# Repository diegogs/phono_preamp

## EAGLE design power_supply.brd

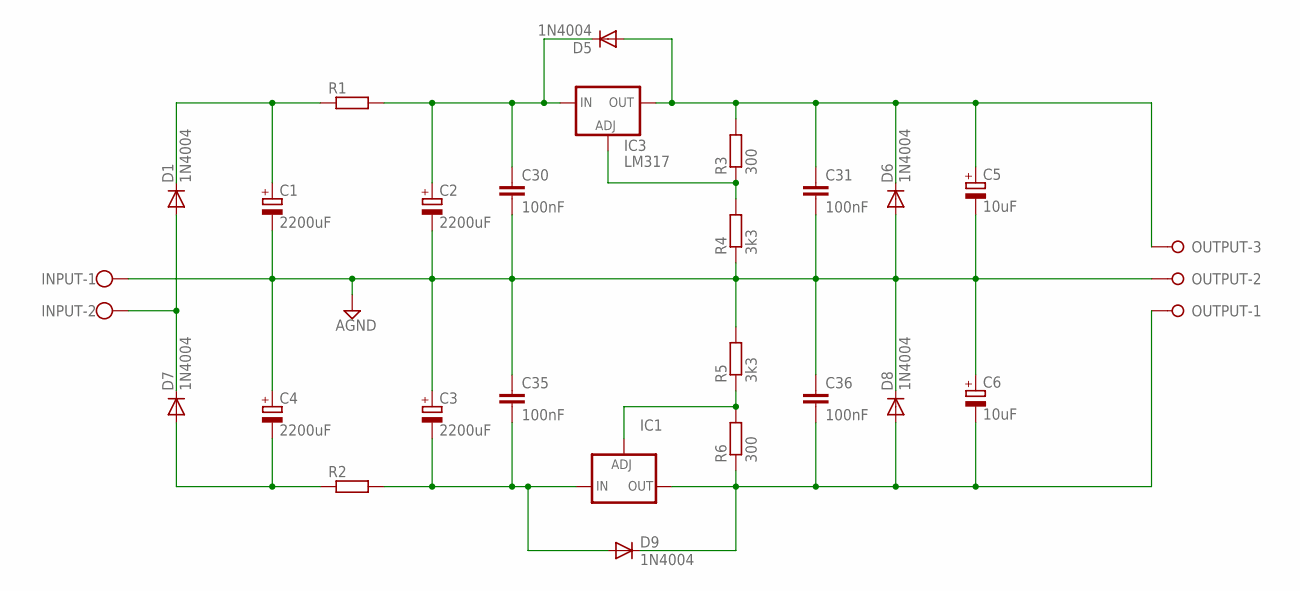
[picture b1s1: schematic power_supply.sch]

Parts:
C1, C2, C3, C4: 2200uF; E7,5-16
C5, C6: 10uF; E2,5-5
C30, C31, C35, C36: 100nF; C050-025X075
D1, D5, D6, D7, D8, D9: 1N4004; DO41-10
IC1: LM337TS; 337TS
IC3: LM317; 317TS
INPUT: W237-102
OUTPUT: W237-3E
R1, R2: R-EU_0207/10; 0207/10
R3, R6: 300; 0207/7
R4, R5: 3k3; 0207/7

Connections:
AGND: C1.-, C2.-, C3.+, C4.+, C5.-, C6.+, C30.2, C31.2, C35.1, C36.1, D6.A, D8.C, INPUT.1, OUTPUT.2, R4.1, R5.2
unnamed: IC1.1 (ADJ), R5.1, R6.2
unnamed: D1.A, D7.C, INPUT.2
unnamed: C6.-, C36.2, D8.A, D9.C, IC1.3 (OUT), OUTPUT.1, R6.1
unnamed: C5.+, C31.1, D5.A, D6.C, IC3.2 (OUT), OUTPUT.3, R3.2
unnamed: C2.+, C30.1, D5.C, IC3.3 (IN), R1.2
unnamed: IC3.1 (ADJ), R3.1, R4.2
unnamed: C1.+, D1.C, R1.1
unnamed: C3.-, C35.2, D9.A, IC1.2 (IN), R2.2
unnamed: C4.-, D7.A, R2.1

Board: 2 copper layers, 26 parts (26 on the bottom side), 10 nets, no tracks yet.

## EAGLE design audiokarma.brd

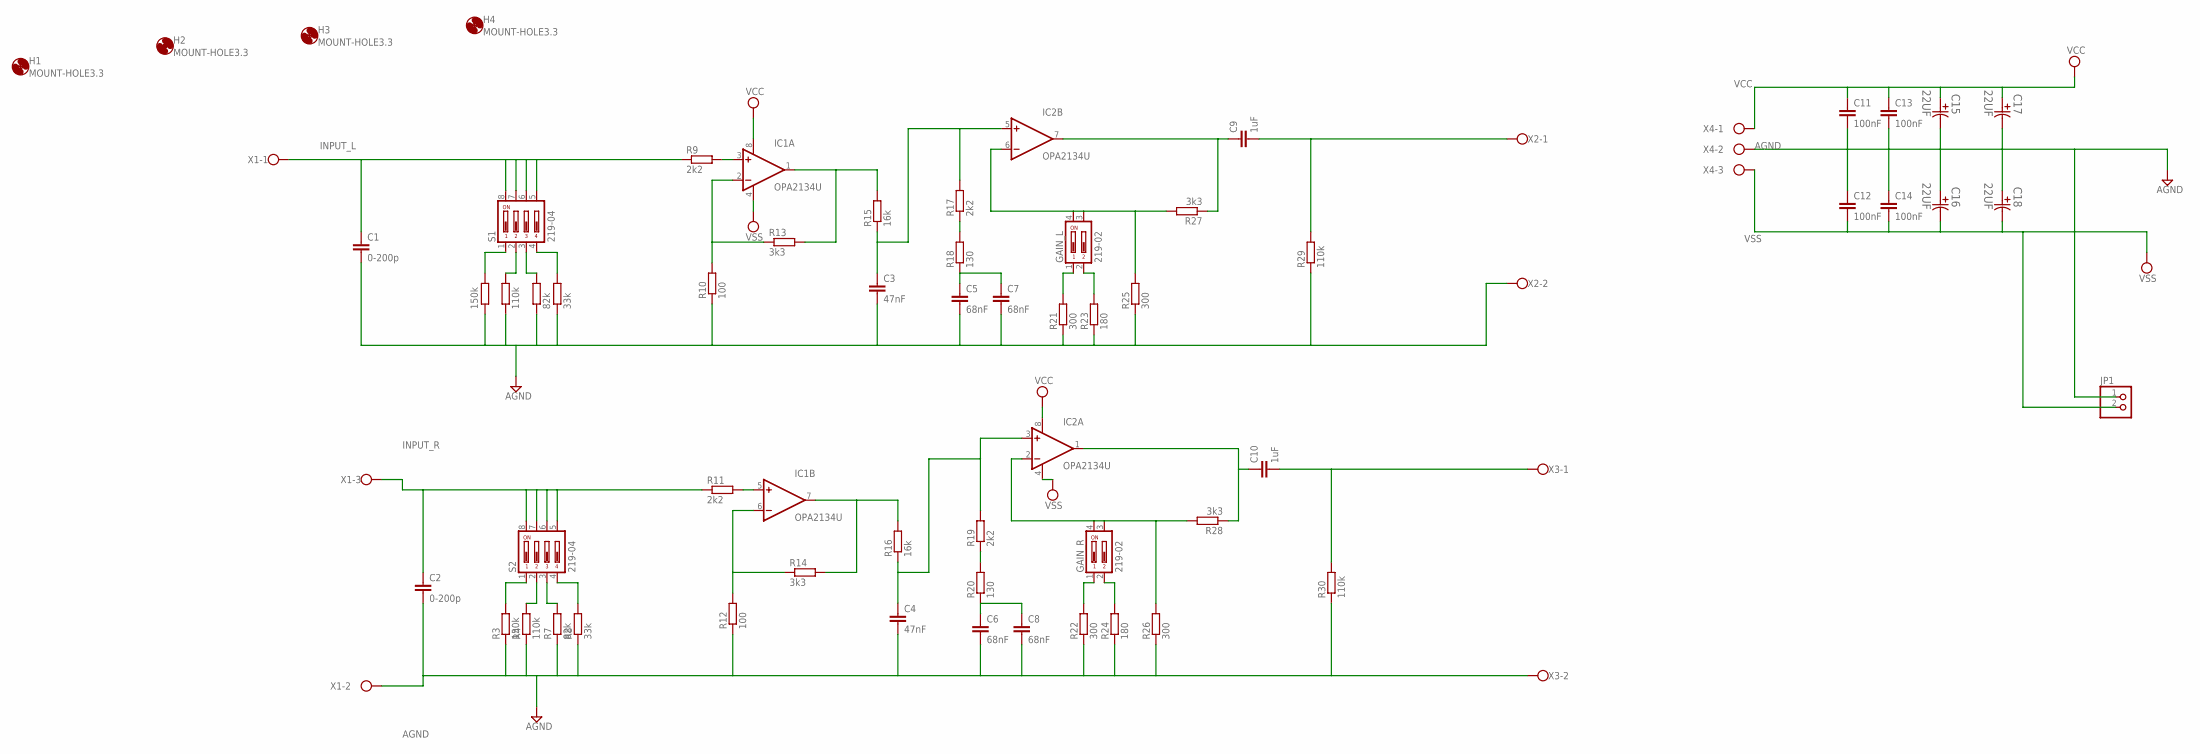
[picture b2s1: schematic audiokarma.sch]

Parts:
C1, C2: 0-200p; C0805
C3, C4: 47nF; C050-025X075
C5, C6, C7, C8: 68nF; C050-035X075
C9, C10: 1uF; C050-050X075
C11, C12, C13, C14: 100nF; C0805
C15, C16, C17, C18: 22UF; CAPAE830X650N
GAIN_L: 219-02; CTS-219-02
GAIN_R: 219-02; CTS-219-02
H1, H2, H3, H4: MOUNT-HOLE3.3; 3,3
IC1, IC2: OPA2134U; SO08
JP1: PINHD-1X2; 1X02
R1, R3: 150k; R0805
R2, R4, R29, R30: 110k; R0805
R5, R7: 82k; R0805
R6, R8: 33k; R0805
R9, R11, R17, R19: 2k2; R0805
R10, R12: 100; R0805
R13, R14, R27, R28: 3k3; R0805
R15, R16: 16k; R0805
R18, R20: 130; R0805
R21, R22, R25, R26: 300; R0805
R23, R24: 180; R0805
S1, S2: 219-04; CTS-219-04
X1, X4: W237-103
X2, X3: W237-102

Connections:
AGND: C1.2, C2.2, C3.2, C4.2, C5.2, C6.2, C7.2, C8.2, C11.2, C12.1, C13.2, C14.1, C15.2, C16.1, C17.2, C18.1, JP1.1, R1.1, R2.1, R3.1, R4.1, R5.1, R6.1, R7.1, R8.1, R10.1, R12.1, R21.1, R22.1, R23.1, R24.1, R25.1, R26.1, R29.1, R30.1, X1.2, X2.2, X3.2, X4.2
INPUT_L: C1.1, R9.1, S1.5, S1.6, S1.7, S1.8, X1.1
INPUT_R: C2.1, R11.1, S2.5, S2.6, S2.7, S2.8, X1.3
unnamed: R1.2, S1.1
unnamed: R2.2, S1.2
unnamed: R5.2, S1.3
unnamed: R6.2, S1.4
unnamed: C9.1, IC2.7 (OUT), R27.1
unnamed: R3.2, S2.1
unnamed: IC1.3 (+IN), R9.2
unnamed: IC1.2 (-IN), R10.2, R13.1
unnamed: C9.2, R29.2, X2.1
unnamed: IC1.1 (OUT), R13.2, R15.2
unnamed: C3.1, IC2.5 (+IN), R15.1, R17.2
unnamed: R4.2, S2.2
unnamed: R7.2, S2.3
unnamed: R8.2, S2.4
unnamed: C5.1, C7.1, R18.1
unnamed: R17.1, R18.2
unnamed: IC1.5 (+IN), R11.2
unnamed 20: GAIN_L.3, GAIN_L.4, IC2.6 (-IN), R25.2, R27.2; also elsewhere on the board
unnamed 21: GAIN_L.1, R21.2; also elsewhere on the board
unnamed 22: GAIN_L.2, R23.2; also elsewhere on the board
unnamed: IC1.6 (-IN), R12.2, R14.1
unnamed: IC1.7 (OUT), R14.2, R16.2
unnamed: C4.1, IC2.3 (+IN), R16.1, R19.2
unnamed: C6.1, C8.1, R20.1
unnamed: R19.1, R20.2
unnamed 28: GAIN_R.3, GAIN_R.4, IC2.2 (-IN), R26.2, R28.2; also elsewhere on the board
unnamed 29: GAIN_R.1, R22.2; also elsewhere on the board
unnamed 30: GAIN_R.2, R24.2; also elsewhere on the board
unnamed: C10.1, IC2.1 (OUT), R28.1
unnamed: C10.2, R30.2, X3.1
VCC: C11.1, C13.1, C15.1, C17.1, IC1.8 (V+), IC2.8 (V+), X4.1
VSS: C12.2, C14.2, C16.2, C18.2, IC1.4 (V-), IC2.4 (V-), JP1.2, X4.3

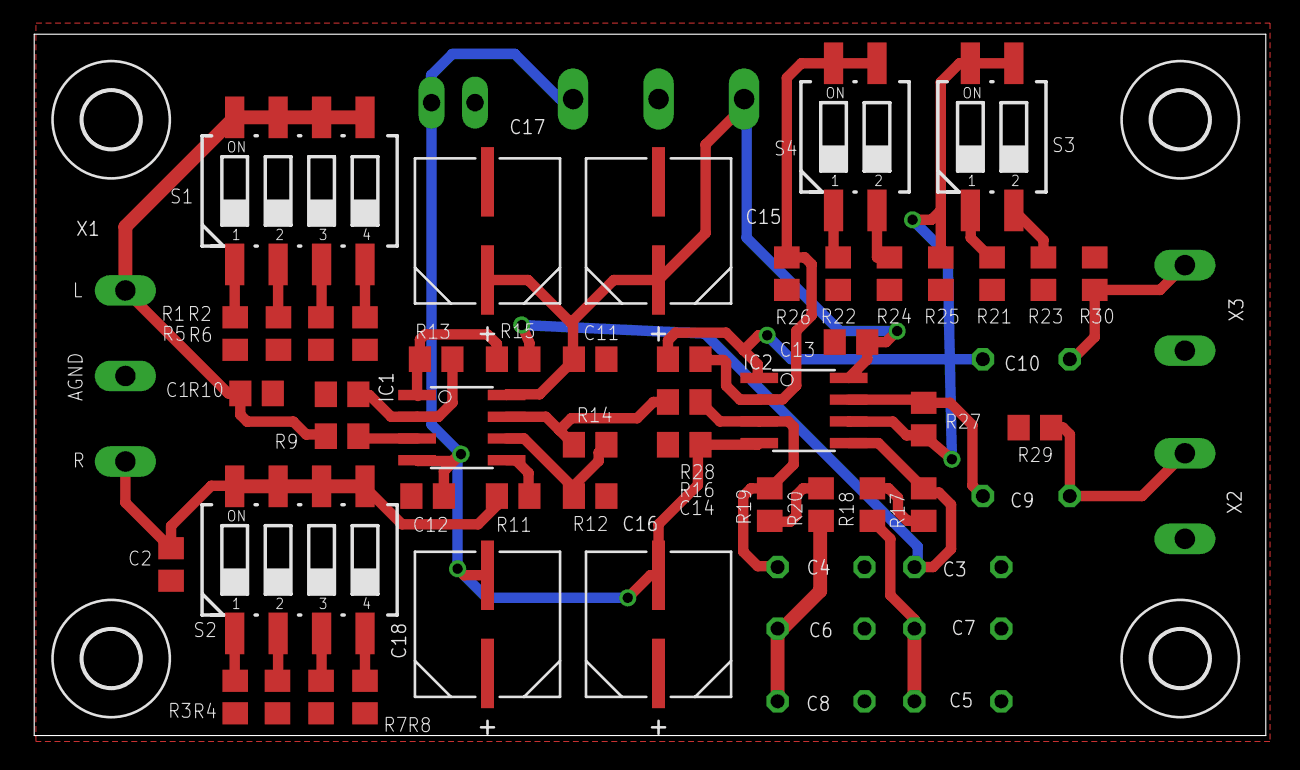
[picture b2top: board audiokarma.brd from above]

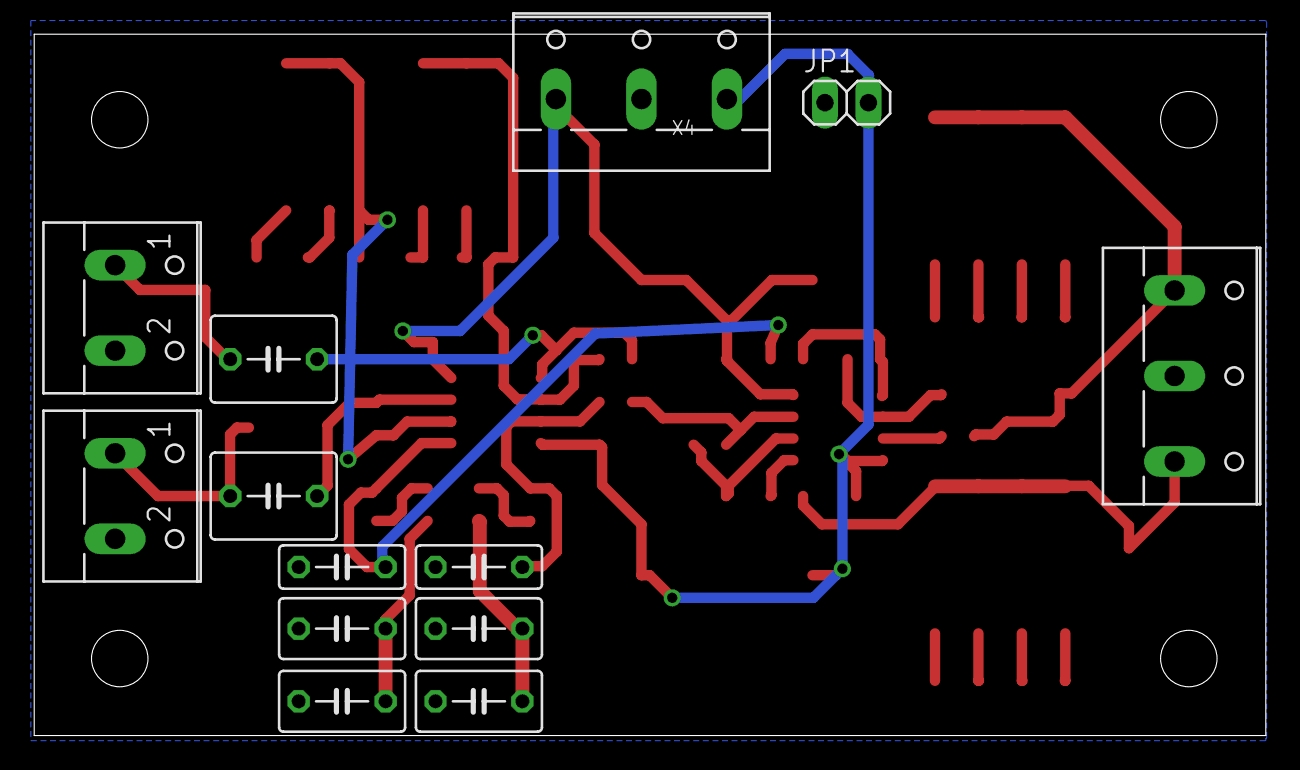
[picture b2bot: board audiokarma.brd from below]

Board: 2 copper layers, 72.0 x 41.0 mm, 63 parts (13 on the bottom side), 35 nets.

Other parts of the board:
S3, S4: 219-02; CTS-219-02

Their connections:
unnamed 20: S3.3, S3.4; also elsewhere on the board
unnamed 21: S3.1; also elsewhere on the board
unnamed 22: S3.2; also elsewhere on the board
unnamed 28: S4.3, S4.4; also elsewhere on the board
unnamed 29: S4.1; also elsewhere on the board
unnamed 30: S4.2; also elsewhere on the board

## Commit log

2016-12-07 :neckbeard: Added .gitattributes & .gitignore files
2016-12-07 primer commit
2016-12-09 esquemático completo
    Por revisar footprints
2016-12-09 rutado al 60%
2016-12-13 colocados al 90%
2016-12-19 rutado 100% pendiente revisión
2016-12-21 Phono100% e inicio de supply
2016-12-22 Fuente posicionada 20%
